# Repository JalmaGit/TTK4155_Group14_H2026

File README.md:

# TTK4155 Group 14 - 2026

TTK4155 Labassignment

Remember to `chmod` and set the correct destination (default `sanntid-1`).

## Development

Activate development environment with `devenv shell`.
Requires `nix` and `devenv`.

Generate compile commands for the LSP with `make compiledb`.

Remember to `make fmt` before committing!

## Logging

### Configure SSH

In `~/.ssh/config`,
set `sanntid-1` to the lab computer/place,
and the correct ip.

```bat
Host sanntid-1
HostName 10.100.23.18
User student
IdentityFile ~/.ssh/id_ed25519
IdentitiesOnly yes
```

### Logging Node 1

```bash
ssh sanntid-1
sudo picocom --baud 9600 --databits 8 --stopbits 2 /dev/ttyS0
```

### Logging Node 2

```bash
ssh sanntid-1
sudo picocom --baud 9600 --databits 8 --parity n --stopbits 1 --flow n /dev/ttyACM0
```

## Flashing

### Node1

```bash
devenv shell

cd node1
make clean && make flash
```

### Node2

```bash
devenv shell

cd node2
make clean && make flash
```

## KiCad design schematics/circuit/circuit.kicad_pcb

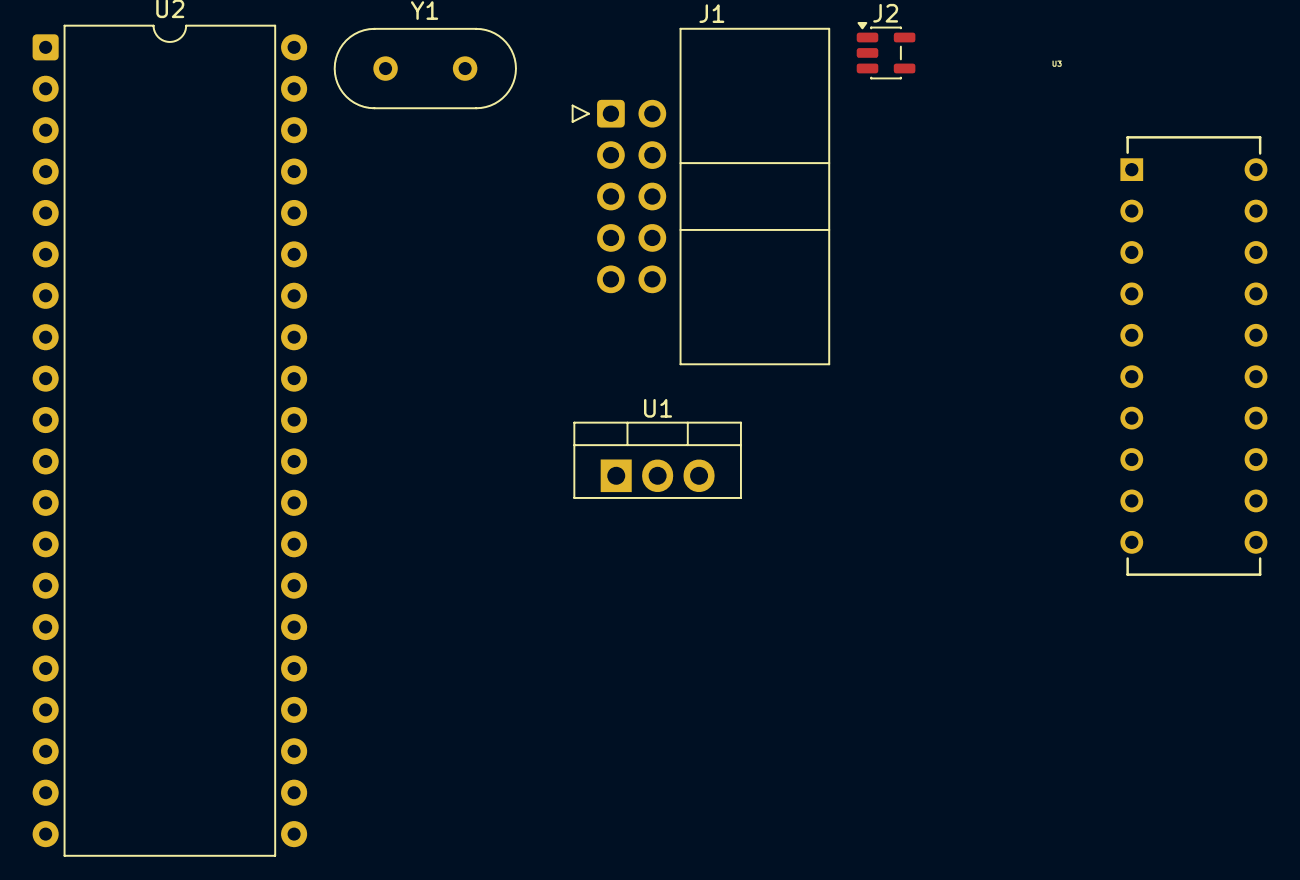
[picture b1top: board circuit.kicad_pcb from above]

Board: 2 copper layers, 6 parts (0 on the bottom side), 15 nets, no tracks yet.

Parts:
J1: AVR-JTAG-10; IDC-Header_2x05_P2.54mm_Horizontal
J2: DE9_Pins; SOT-23-5
U1: LM7805_TO220; TO-220-3_Vertical
U2: ATmega162-16P; DIP-40_W15.24mm
U3: MAX233CPP; 21-0043D_20
Y1: Crystal; Crystal_HC49-U_Vertical

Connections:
+5V: J1.4 (VREF), U1.3 (VO), U2.40 (VCC), U3.7 (VCC)
Earth: J1.2 (GND), J1.10 (GND), J2.5, U1.2 (GND), U2.20 (GND), U3.6 (GND_2), U3.9 (GND)
unnamed: U2.19 (XTAL1), Y1.2
unnamed: U2.18 (XTAL2), Y1.1
unnamed: U3.11 (C2+_2), U3.15 (C2+)
unnamed: U3.10 (CS-), U3.16 (C2-)
unnamed: J2.2, U3.3 (R1OUT)
unnamed: J2.3, U3.5 (T1OUT)
unnamed: U3.12 (V-_2), U3.17 (V-)
TCK: J1.1 (TCK), U2.25 (PC4)
TDI: J1.9 (TDI), U2.28 (PC7)
TDO: J1.3 (TDO), U2.27 (PC6)
TMS: J1.5 (TMS), U2.26 (PC5)
UART_RX: U2.3 (PB2), U3.4 (R1IN)
UART_TX: U2.4 (PB3), U3.2 (T1IN)
